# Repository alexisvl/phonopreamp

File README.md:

# PA1-P06 phono preamplifier

This is my spin on the well known [Elliott Sound Products] "Project 06" phono preamp, with integrated power supply, a couple modifications, and an acrylic sandwich enclosure.

[LICENSE] NOTE: The original ESP P06 is not licensed for reuse in any way. This variant uses only the filter chain topology and component values, neither of which are directly copyrightable, but **please** respect the original designer's (and my) wishes: my version is licensed CC BY-NC-SA, that is the most restrictive of all Creative Commons licenses and forbids commercial use even if you were to follow all the usual open-source rules! Both ESP and I are explicitly requesting you not make money off this design. It's not terribly hard to figure out how to implement the RIAA curves for yourself if you want a commercial product. Don't mooch, filthy capitalist pigs.

The CAD files were created with a development build of KiCad from April 2020; a release build may not load them properly.

[![3D render][render_small]](../master/phonopreamp.png)

- [Schematic]
- [BOM] in Digi-Key bulk add format

## Revision B

This repository includes a Revision B, which I have not yet actually built. See the [changelog] for more information.

## Gerbers

Gerbers currently don't exist in this repository. Recent KiCad builds have had a bug with Gerber export that bit me when I was having this board made and I don't want to go posting files until I'm more confident. Generate yourself, at your own risk.

## Assembly tips

- The mounting screw near the input jacks is meant to be the anchor point for a ground wire. I added a solder lug and heatshrink to the phono ground lead, then put the lug between screw and washer in that corner.
- Build the board as a sandwich: M3×0.5 screw, through nylon or fiber washer (I used [RPC10339-ND]), through acrylic base plate, into short standoff, through PCB, into long standoff (see BOM). From the top, M3×0.5 screw, through washer, through acrylic top plate, into standoff. On the ground terminal corner, the ground lug goes between the top screw and washer.
    - Washers are necessary to prevent _cracking_ the acrylic (I'm not just being picky about scratches), and should be soft washers. These will give slightly if the screws are over-tightened, both preventing excessive pressure on the acrylic, as well as compressing to lock the screws in place better.
    - Short standoffs are omitted from BOM because I ordered the wrong ones and improvized with a couple nuts — I don't have a part number. They should be about 5mm long.
- The PPS film capacitors are, to be polite, a complete bitch to stuff. They're basically unsolderable as they melt easily, and are moisture sensitive too. The method I used is: assemble entire board except these using water soluble flux; wash very well to keep clean. Carefully spot-solder film capacitors with no-clean flux, low temperature, quickly, being careful not to touch the sides with the iron, squish with tweezers, or keep hot too long. Do not wash.
    - If you don't care about cleaning the flux, just use no-clean for the whole board and resist any temptation to clean it.

### Assembled stack:

```
|>----    |    ##    [===]---    ##    [===============]    ##    |          -----<|
               ##                ##                         ##
               ##                ##                         ##
               ##                ##                         ##
               ##                ##                         ##
               ##                ##                         ##
|>----    |    ##    [===]---    ##    [===============]    ##    |    ||    -----<|

^         ^    ^     ^           ^     ^                    ^     ^    ^     ^
|         |    |     |           |     |                    |     |    |     M3×0.5 screws
|         |    |     |           |     |                    |     |    ground lug (input corner only)
|         |    |     |           |     |                    |     nylon washers
|         |    |     |           |     |                    top acrylic plate
|         |    |     |           PCB   long F-F standoffs
|         |    |     short F-M standoffs
|         |    bottom acrylic plate
|         nylon washers
M3×0.5 screws
```

[Elliott Sound Products]: http://sound-au.com/project06.htm
[Schematic]: ../master/phonopreamp.pdf
[LICENSE]: ../master/COPYING
[changelog]: ../master/CHANGELOG
[render_small]: ../master/phonopreamp_small.png
[BOM]: ../master/phonopreamp/bom.txt
[RPC10339-ND]: https://www.digikey.com/product-detail/en/essentra-components/16M03080080/RPC10339-ND/10299235

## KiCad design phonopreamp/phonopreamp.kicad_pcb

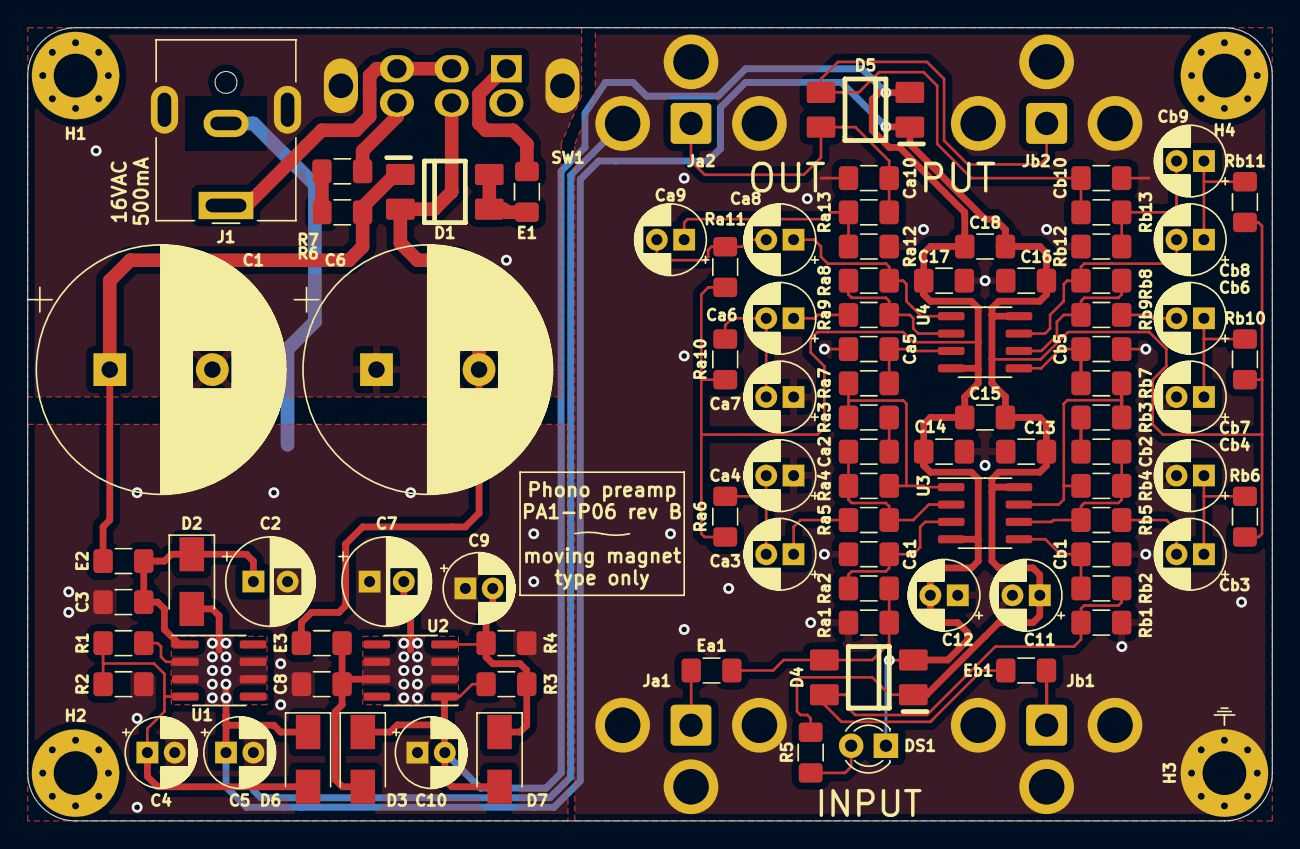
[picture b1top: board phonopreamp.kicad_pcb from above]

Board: 2 copper layers, 91.0 x 58.0 mm, 99 parts (1 on the bottom side), 47 nets.

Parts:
C1, C6: 2200µ; CP_Radial_D18.0mm_P7.50mm
C2, C7: 68µ; CP_Radial_D6.3mm_P2.50mm
C3, C8, C13, C14, C15, C16, C17, C18: 100n; C_1206_3216Metric_Pad1.42x1.75mm_HandSolder
C4, C9: 10µ; CP_Radial_D5.0mm_P2.00mm
C5, C10, C11, C12: 100µ; CP_Radial_D5.0mm_P2.00mm
Ca1: 22p; C_1206_3216Metric_Pad1.42x1.75mm_HandSolder
Ca2, Ca5, Ca10: 22n/2%; C_1206_3216Metric_Pad1.42x1.75mm_HandSolder
Ca3, Ca4, Ca6, Ca7, Ca8, Ca9: 47µ; CP_Radial_D5.0mm_P2.00mm
Cb1: 22p; C_1206_3216Metric_Pad1.42x1.75mm_HandSolder
Cb2, Cb5, Cb10: 22n/2%; C_1206_3216Metric_Pad1.42x1.75mm_HandSolder
Cb3, Cb4, Cb6, Cb7, Cb8, Cb9: 47µ; CP_Radial_D5.0mm_P2.00mm
D1, D4, D5: MB10F; MBxS
D2, D3, D6, D7: S1G; D_SMA
DS1: RED; LED_D3.0mm
E1, E2, E3: 600; L_1206_3216Metric_Pad1.42x1.75mm_HandSolder
Ea1: 600; L_1206_3216Metric_Pad1.42x1.75mm_HandSolder
Eb1: 600; L_1206_3216Metric_Pad1.42x1.75mm_HandSolder
G1: BY-NC-SA; Logo_silk_CC-BY-NC-SA_10x3.6mm
H1, H2, H3, H4: MountingHole; MountingHole_3.2mm_M3_Pad_Via
J1: 16VAC; BarrelJack_CUI_PJ-063AH_Horizontal
Ja1: IN_L; RCJ-01x
Ja2: OUT_L; RCJ-01x
Jb1: IN_R; RCJ-01x
Jb2: OUT_R; RCJ-01x
R1, R3: 240/1%; R_1206_3216Metric_Pad1.42x1.75mm_HandSolder
R2, R4: 2k43/1%; R_1206_3216Metric_Pad1.42x1.75mm_HandSolder
R5: 10k; R_1206_3216Metric_Pad1.42x1.75mm_HandSolder
R6, R7: 240; R_1206_3216Metric_Pad1.42x1.75mm_HandSolder
Ra1: 47k; R_1206_3216Metric_Pad1.42x1.75mm_HandSolder
Ra2: 4k7; R_1206_3216Metric_Pad1.42x1.75mm_HandSolder
Ra3: 10k/1%; R_1206_3216Metric_Pad1.42x1.75mm_HandSolder
Ra4: 180k/1%; R_1206_3216Metric_Pad1.42x1.75mm_HandSolder
Ra5: 4k7/1%; R_1206_3216Metric_Pad1.42x1.75mm_HandSolder
Ra6, Ra10, Ra11: 470k; R_1206_3216Metric_Pad1.42x1.75mm_HandSolder
Ra7: 3k4/1%; R_1206_3216Metric_Pad1.42x1.75mm_HandSolder
Ra8: 100k/1%; R_1206_3216Metric_Pad1.42x1.75mm_HandSolder
Ra9: 2k7/1%; R_1206_3216Metric_Pad1.42x1.75mm_HandSolder
Ra12: 100k; R_1206_3216Metric_Pad1.42x1.75mm_HandSolder
Ra13: 620; R_1206_3216Metric_Pad1.42x1.75mm_HandSolder
Rb1: 47k; R_1206_3216Metric_Pad1.42x1.75mm_HandSolder
Rb2: 4k7; R_1206_3216Metric_Pad1.42x1.75mm_HandSolder
Rb3: 10k/1%; R_1206_3216Metric_Pad1.42x1.75mm_HandSolder
Rb4: 180k/1%; R_1206_3216Metric_Pad1.42x1.75mm_HandSolder
Rb5: 4k7/1%; R_1206_3216Metric_Pad1.42x1.75mm_HandSolder
Rb6, Rb10, Rb11: 470k; R_1206_3216Metric_Pad1.42x1.75mm_HandSolder
Rb7: 3k4/1%; R_1206_3216Metric_Pad1.42x1.75mm_HandSolder
Rb8: 100k/1%; R_1206_3216Metric_Pad1.42x1.75mm_HandSolder
Rb9: 2k7/1%; R_1206_3216Metric_Pad1.42x1.75mm_HandSolder
Rb12: 100k; R_1206_3216Metric_Pad1.42x1.75mm_HandSolder
Rb13: 620; R_1206_3216Metric_Pad1.42x1.75mm_HandSolder
SW1: MFS201N-16-Z
U1: LM317LMX; SOIC-8_3.9x4.9mm_P1.27mm
U2: LM337LMX; SOIC-8_3.9x4.9mm_P1.27mm
U3, U4: LM4562; SOIC-8_3.9x4.9mm_P1.27mm

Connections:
+14V: C5.1, C11.1, C13.1, C15.1, C16.1, C18.1, D2.2 (A), D4.1 (+), D5.1 (+), D6.1 (K), R1.2, R5.2, Rb6.1, Rb10.1, Rb11.1, U1.2 (VO), U1.3 (VO), U1.6 (VO), U1.7 (VO), U3.8 (V+), U4.8 (V+)
-14V: C10.2, C12.2, C14.1, C15.2, C17.1, C18.2, D3.1 (K), D4.2 (-), D5.2 (-), D7.2 (A), DS1.1 (K), R3.1, Ra6.1, Ra10.1, Ra11.1, U2.1 (VO), U3.4 (V-), U4.4 (V-)
/VIN+: C2.1, C3.1, D2.1 (K), E2.2, U1.1 (VI)
/VIN-: C7.2, C8.2, D3.2 (A), E3.2, U2.2 (VI), U2.3 (VI), U2.6 (VI), U2.7 (VI)
GND: C1.2, C2.2, C3.2, C4.2, C5.2, C6.1, C7.1, C8.1, C9.1, C10.1, C11.2, C12.1, C13.2, C14.2, C16.2, C17.2, Ca1.2, Ca4.1, Ca5.1, Ca7.1, Ca10.1, Cb1.2, Cb4.2, Cb5.1, Cb7.2, Cb10.1, H3.1, J1.2, J1.MP (MountPin), Ja1.2 (Ext), Ja2.2 (Ext), Jb1.2 (Ext), Jb2.2 (Ext), R2.1, R4.2, Ra1.1, Ra12.1, Rb1.1, Rb12.1, SW1.SH
unnamed: C1.1, D1.1 (+), E2.1, R6.2
unnamed: C4.1, D6.2 (A), R1.1, R2.2, U1.4 (ADJ)
unnamed: C6.2, D1.2 (-), E3.1, SW1.5 (B)
unnamed: C9.2, D7.1 (K), R3.2, R4.1, U2.4 (ADJ)
unnamed: Ca1.1, Ra2.2, U3.3 (+)
unnamed: Ca2.1, Ra4.1, Ra5.2, U3.2 (-)
unnamed: Ca2.2, Ra3.1
unnamed: Ca3.1, Ra5.1
unnamed: Ca3.2, Ca4.2, Ra6.2
unnamed: Ca5.2, Ra7.2, U4.3 (+)
unnamed: Ca6.1, Ra9.1
unnamed: Ca6.2, Ca7.2, Ra10.2
unnamed: Ca8.1, Ra8.2, U4.1
unnamed: Ca8.2, Ca9.2, Ra11.2
unnamed: Ca9.1, Ra12.2, Ra13.1
unnamed: Ca10.2, D5.4 (~~), Ja2.1 (In), Ra13.2
unnamed: Cb1.1, Rb2.2, U3.5 (+)
unnamed: Cb2.1, Rb4.1, Rb5.2, U3.6 (-)
unnamed: Cb2.2, Rb3.1
unnamed: Cb3.1, Cb4.1, Rb6.2
unnamed: Cb3.2, Rb5.1
unnamed: Cb5.2, Rb7.2, U4.5 (+)
unnamed: Cb6.1, Cb7.1, Rb10.2
unnamed: Cb6.2, Rb9.1
unnamed: Cb8.1, Cb9.1, Rb11.2
unnamed: Cb8.2, Rb8.2, U4.7
unnamed: Cb9.2, Rb12.2, Rb13.1
unnamed: Cb10.2, D5.3 (~~), Jb2.1 (In), Rb13.2
unnamed: D1.3 (~~), D1.4 (~~), E1.2
unnamed: D4.3 (~~), Ea1.2, Ra1.2, Ra2.1
unnamed: D4.4 (~~), Eb1.2, Rb1.2, Rb2.1
unnamed: DS1.2 (A), R5.1
unnamed: E1.1, SW1.1 (A)
unnamed: Ea1.1, Ja1.1 (In)
unnamed: Eb1.1, Jb1.1 (In)
unnamed: J1.1, SW1.2 (B), SW1.3 (C)
unnamed: R6.1, R7.1
unnamed: R7.2, SW1.6 (C)
unnamed: Ra3.2, Ra4.2, Ra7.1, U3.1
unnamed: Ra8.1, Ra9.2, U4.2 (-)
unnamed: Rb3.2, Rb4.2, Rb7.1, U3.7
unnamed: Rb8.1, Rb9.2, U4.6 (-)

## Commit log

2020-04-30 Release revision B
2020-04-30 Add gerbers note
2020-04-30 Update BOM for rev B
2020-04-30 Add assembly tips
